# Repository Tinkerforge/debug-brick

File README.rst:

Debug Brick
===========

This repository contains the hardware design files.

Repository Content
------------------

hardware/:
 * Contains KiCad project files and additionally schematics as PDF

Hardware
--------

The hardware is designed with the open source EDA Suite KiCad
(http://www.kicad.org). Before you are able to open the files,
you have to install the Tinkerforge kicad-libraries
(https://github.com/Tinkerforge/kicad-libraries). You can either clone
them directly in hardware/ or clone them in a separate folder and
symlink them into hardware/
(ln -s kicad_path/kicad-libraries project_path/hardware). After that you
can open the .pro file in hardware/ with KiCad and from there view and
modify the schematics and the PCB layout.

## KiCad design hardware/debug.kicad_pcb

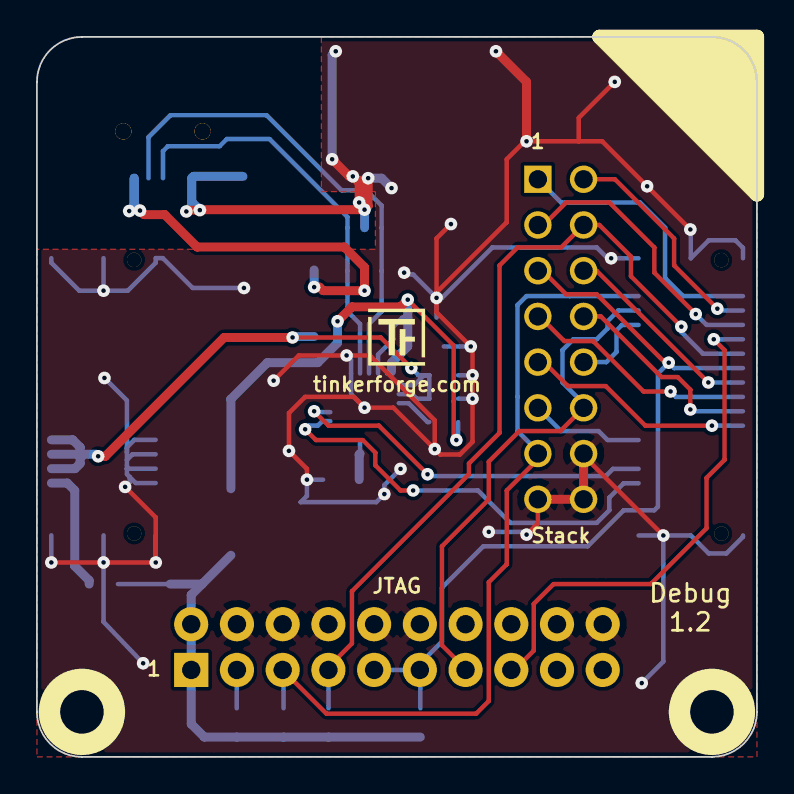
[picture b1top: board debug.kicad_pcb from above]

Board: 2 copper layers, 40.0 x 40.0 mm, 25 parts (0 on the bottom side), 27 nets.

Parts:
C1, C2, C5: 100nF; C0603
C3, C4: 4.7µF/10V; C0805
D1, D2: B0520LW; SOD-123
J1, J3: STACK-DOWN; BTB08-ACS-BTM
J2: USB-MINI-B-SMD
P1: CONN_16; pin_array_8x2
P2: JTAG; pin_array_10x2
R1, R2, R3, R4: 100k; R0603
R5: 4k7; R0603
R6: 0; R0603
U1: CM1293A; SC-74
U2: CP2104; QFN-24-4x4-EP
U3, U4, U5: DRILL; DRILL_NP
VAL: CE_5mm
VAL#2: WEEE_7mm

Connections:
+3V3: D2.2, P2.1, P2.2, R1.1, R2.1, R3.1, R4.1, R6.2
+5V: C1.1, C2.1, D1.2, J3.22, J3.24, J3.26, U2.7, U2.8
EX-SEL: J1.22, P1.11
GND: C1.2, C2.2, C3.2, C4.2, C5.2, J1.EP, J2.5, J2.6, J3.21, J3.23, J3.25, J3.27, J3.EP, P1.14, P1.15, P1.16, P2.4, P2.6, P2.8, P2.10, P2.12, P2.14, P2.16, P2.18, P2.20, U1.2, U2.2, U2.25
unnamed: C3.1, U2.16
unnamed: C4.1, C5.1, D2.1, R5.2, U2.5, U2.6
unnamed: D1.1, J2.1, U1.5
unnamed: J1.1, P1.1
unnamed: J1.3, P1.2
unnamed: J1.5, P1.3
unnamed: J1.7, P2.15
unnamed: J1.9, P1.4, P2.7, R2.2
unnamed: J1.11, P1.5, P2.9, P2.11, R3.2
unnamed: J1.13, P1.6
unnamed: J1.15, P1.7
unnamed: J1.17, P1.8
unnamed: J1.19, P1.9
unnamed: J2.2, U1.3, U1.4, U2.4
unnamed: J2.3, U1.1, U1.6, U2.3
unnamed: J3.28, R6.1
unnamed: P2.3, R4.2
unnamed: R5.1, U2.9
RXD: J1.26, U2.21
SCL: J1.4, P1.12, P2.13
SDA: J1.2, P1.13, P2.5, R1.2
SEL: J1.6, P1.10
TXD: J1.28, U2.20

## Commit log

2011-08-26 add repository description
2015-03-26 next generation of debug brick hardware files
2017-04-28 Add all 3d information
    move conn components to kicad-libraries
2017-04-28 Add 3D model for Debug Brick 1.2
2018-02-20 Add .gitignore
2018-02-20 Cleanup KiCad libraries config
    Ensure LibDir=kicad-libraries and LibName1=tinkerforge.
    Remove special library.
2018-07-25 Add new 3d model
2021-10-25 Update KiCad link
    https://www.kicad.org/blog/2021/10/Avoid-links-to-former-kicad-domain/

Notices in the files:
hardware/debug.kicad_pcb:
Licensed under CERN OHL v.1.1
Copyright (©) 2015, B.Nordmeyer
Copyright Tinkerforge GmbH 2015.
This documentation describes Open Hardware and is licensed under the
CERN OHL v. 1.1.
